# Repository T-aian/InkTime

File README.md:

# Documentație de Arhitectură și Inginerie Hardware: Sistemul Wearable InkTime

## 1. Introducere

Proiectul InkTime reprezintă o inițiativă tehnologică ambițioasă de a dezvolta un smartwatch open-source, optimizat pentru costuri reduse și manufacturabilitate la scară largă, fără a face compromisuri în ceea ce privește fiabilitatea sau performanța.

### 1.1. Structura Proiectului

- **Hardware/**: Găzduiește definițiile fundamentale ale circuitului. Aici se regăsesc fișierul schematic (.sch), alături de fișierul board-ului (.brd).
- **Manufacturing/**: Conține arhiva esențială pentru fabrica de PCB-uri (gerbers.zip), care include straturile de cupru, măștile de lipire (solder mask), stratul de inscripționare (silkscreen) și fișierele de găurire (Excellon drill files). De asemenea, acest director include fișierul Bill of Materials (.bom), detaliind componentele utilizate, și fișierul Pick and Place (.cpl), care mapează coordonatele carteziene (X, Y) și rotația fiecărei componente pentru echipamentele automate de asamblare.
- **Mechanical/**: Include modelul 3D integrat al dispozitivului în format .step și format nativ Fusion360. Acest model cuprinde PCB-ul populat cu componente, geometria exactă a bateriei Li-Po, ecranul LCD, motorul haptic (shaker) și șasiul carcasei într-o vizualizare detaliată de tip "exploded view".
- **Images/**: Un director vizual care conține randări fotorealiste ale PCBA-ului (Printed Circuit Board Assembly) și ilustrează modul de potrivire mecanică a plăcii în carcasă, servind drept ghid vizual pentru procedurile de asamblare manuală.

## 2. Arhitectura de Sistem și Diagrama Bloc

Filosofia de design a smartwatch-ului InkTime se bazează pe o topologie modulară, distribuită în jurul unui nod central de procesare (System-on-Chip). Diagrama bloc de mai jos ilustrează interconectarea magistralelor de date, a traseelor de putere și a modulelor periferice. Sistemul este împărțit în patru domenii funcționale majore: Domeniul de Putere (Power Tree), Domeniul de Procesare și Comunicație RF, Domeniul Senzorial și Domeniul Interfeței cu Utilizatorul (UI/HMI).

Fluxul de operare este dictat de nRF52840, care gestionează stările de energie (Power States) ale întregului sistem. Modulul comunică asincron prin magistrala I2C (Inter-Integrated Circuit) cu senzorii (BMA423 pentru detecția mișcării, MAX17048 pentru starea bateriei, DRV2605 pentru feedback haptic) și sincron prin magistrala SPI (Serial Peripheral Interface) cu ecranul LCD. Etajul de alimentare separă procesul de încărcare (gestionat autonom de BQ25121A) de procesul de reglare a tensiunii (gestionat de RT6150AWSC), asigurând o tensiune logică de 3.3V indiferent de nivelul de descărcare al bateriei.

## 3. Bill of Materials (BOM)
Realizarea unui dispozitiv de masă la un cost competitiv impune o selecție a componentelor ancorată puternic în realitățile lanțului de aprovizionare (Supply Chain). Toate componentele majore au fost selectate din biblioteca producătorului asiatic JLCPCB, favorizând componentele "Basic" sau "Extended" aflate constant în stoc, evitând astfel întârzierile de aprovizionare.

De asemenea, pachetele fizice (footprints) au fost alese pentru a permite un asamblaj automatizat de mare viteză pe mașinile Pick and Place, respectând totodată cerința impusă de a utiliza exclusiv pachete SMD (Surface Mount Device).

| Componentă        | Descriere funcțională                                                                                      | JLCPCB Part #    | Link JLCPCB | Datasheet                                                                                                                                                                                                  |
| ----------------- | ---------------------------------------------------------------------------------------------------------- | ---------------- | ----------- | ---------------------------------------------------------------------------------------------------------------------------------------------------------------------------------------------------------- |
| nRF52840-QIAA-R   | System-on-Chip (SoC) ARM Cortex-M4F 64MHz, transceiver Bluetooth 5.0, 1MB Flash, 256KB RAM, pachet AQFN-73 | C190794          | [Link JLCPCB](https://jlcpcb.com/partdetail/NordicSemicon-NRF52840_QIAAR/C190794) | [https://files.seeedstudio.com/wiki/XIAO-BLE/Nano_BLE_MCU-nRF52840_PS_v1.1.pdf](https://files.seeedstudio.com/wiki/XIAO-BLE/Nano_BLE_MCU-nRF52840_PS_v1.1.pdf)                                             |
| MAX17048G+T10     | Fuel Gauge pentru baterii Li-Ion (1 celulă), algoritm ModelGauge, interfață I2C, pachet TDFN-8             | C2682616         | [Link JLCPCB](https://jlcpcb.com/partdetail/C2682616) | [https://www.analog.com/media/en/technical-documentation/data-sheets/max17048-max17049.pdf](https://www.analog.com/media/en/technical-documentation/data-sheets/max17048-max17049.pdf)                     |
| BMA423            | Accelerometru MEMS triaxial, 12 biți, step counter hardware, pachet LGA-12                                 | C189517          | [Link JLCPCB](https://www.lcsc.com/product-detail/C189517.html) | [https://watchy.sqfmi.com/assets/files/BST-BMA423-DS000-1509600-950150f51058597a6234dd3eaafbb1f0.pdf](https://watchy.sqfmi.com/assets/files/BST-BMA423-DS000-1509600-950150f51058597a6234dd3eaafbb1f0.pdf) |
| DRV2605YZFR       | Driver haptic smart-loop pentru motoare ERM/LRA, librărie Immersion, pachet DSBGA-9                        | C81079           | [Link JLCPCB](https://www.lcsc.com/product-detail/C81079.html) | [https://www.ti.com/lit/ds/symlink/drv2605.pdf](https://www.ti.com/lit/ds/symlink/drv2605.pdf)                                                                                                             |
| BQ25121AYBGR      | PMIC + încărcător Li-Po ultra low power (max 300mA), Ship Mode, pachet DSBGA-25                            | C111776          | [Link JLCPCB](https://jlcpcb.com/parts) | [https://www.ti.com/lit/ds/symlink/bq25121a.pdf](https://www.ti.com/lit/ds/symlink/bq25121a.pdf)                                                                                                           |
| RT6150AWSC        | Convertor DC-DC buck-boost (1.8V–5.5V → 3.3V), curent max 800mA, consum idle 60µA                          | C147971          | [Link JLCPCB](https://www.lcsc.com/product-detail/C147971.html) | [https://www.richtek.com/assets/product_file/RT6150A=RT6150B/DS6150AB-04.pdf](https://www.richtek.com/assets/product_file/RT6150A=RT6150B/DS6150AB-04.pdf)                                                 |
| KH-TYPE-C-16P     | Conector USB Type-C mamă, 16 pini, SMD, profil redus, 3A                                                   | C709357          | [Link JLCPCB](https://jlcpcb.com/partdetail/KH-TYPE-C-16P/C709357) | N/A                                                                                                                                                                                                        |
| USBLC6-2SC6       | Protecție ESD (TVS diode array), capacitance 2.5pF pentru linii USB                                        | C7519 / C2827654 | [Link JLCPCB](https://jlcpcb.com/partdetail/STMicroelectronics-USBLC62SC6/C7519) | [https://www.st.com/resource/en/datasheet/usblc6-2.pdf](https://www.st.com/resource/en/datasheet/usblc6-2.pdf)                                                                                             |
| 2450AT18B100E     | Antenă ceramică RF 2.45 GHz, eficiență ~76%, pachet SMD 1206                                               | C2836414         | [Link JLCPCB](https://jlcpcb.com/partdetail/JohansonTechnology-2450AT18B100/C2836414) | [https://www.johansontechnology.com/docs/1187/2450AT18B100_X8XXogU.pdf](https://www.johansontechnology.com/docs/1187/2450AT18B100_X8XXogU.pdf)                                                             |

## 4. Descrierea Exhaustivă a Funcționalității Hardware
Sistemul hardware a fost proiectat având ca prioritate absolută optimizarea balanței dintre performanța de calcul, capacitatea de interacțiune umană fluidă și un consum energetic de tip "ultra-low power". Modul în care aceste subsisteme interacționează determină direct fezabilitatea comercială a smartwatch-ului InkTime.
### 4.1. Nucleul de Procesare și Comunicație RF (nRF52840)
La baza sistemului se află integratul nRF52840-QIAA-R, un System-on-Chip (SoC) hibrid care combină logica unui microcontroler cu un transceiver radio de mare performanță. Funcționând la o frecvență de bază de 64 MHz, nucleul ARM Cortex-M4 include o unitate de calcul în virgulă mobilă (FPU - Floating Point Unit), esențială pentru procesarea accelerată a datelor senzoriale tridimensionale (cum ar fi cele generate de BMA423) și randarea elementelor grafice pe afișaj. Dispune de 1 MB memorie Flash internă și 256 KB memorie SRAM. Spațiul generos de memorie Flash permite integrarea sistemelor de operare de tip RTOS (precum Zephyr, frecvent utilizat în comunitatea open-source smartwatch) și implementarea de actualizări Over-The-Air (OTA) sigure.

Componenta de radiofrecvență a SoC-ului este extrem de performantă, suportând tehnologia Bluetooth 5.0 Low Energy (BLE), alături de protocoale precum Thread, Zigbee și rețele proprietare de 2.4 GHz. Dispozitivul are o sensibilitate de recepție de -95 dBm la 1 Mbps și poate emite semnale la o putere configurabilă de la -20 dBm până la +8 dBm. Această versatilitate asigură că ceasul poate menține o legătură stabilă cu un terminal mobil (ex. smartphone) chiar și în medii electromagnetice congestionate, minimizând totodată consumul bateriei adaptând puterea de transmisie. Securitatea pachetelor de date BLE este garantată de coprocesorul intern ARM TrustZone CryptoCell 310, care realizează criptare hardware AES/ECB asincron, degrevând procesorul principal.

Antena ceramică tip SMD (2450AT18B100E) este montată la extremitatea plăcii și este un dispozitiv de tip LTCC (Low Temperature Co-fired Ceramic), proiectat de Johanson Technology. Oferind o eficiență de 76%, antena necesită un design restrictiv al planului de masă pentru a nu-și altera impedanța caracteristică de 50 Ohmi.

### 4.2. Topologia de Alimentare și Managementul Bateriei (Power Delivery Network)

Tensiunea unei baterii clasice Litiu-Polimer (Li-Po) fluctuează considerabil în timpul ciclului său de descărcare, de la o valoare maximă de ~4.2V (complet încărcată) până la o tensiune de cut-off de aproximativ 3.0V. Pentru ca ecranul IPS și procesorul să ruleze constant, au nevoie de o sursă stabilă de energie. Aici intervine arhitectura "Power Tree" a dispozitivului InkTime.

### Etajul de Încărcare și Protecție (BQ25121A și USBLC6-2SC6):

Energia pătrunde în sistem prin intermediul conectorului KH-TYPE-C-16P, o versiune orizontală SMD care susține curenți nominali ridicați și care a fost preferată pentru profilul său plat. Liniile de date și alimentare ale portului USB sunt expuse mediului extern, devenind vulnerabile la descărcări electrostatice (ESD). Circuitul USBLC6-2SC6, conectat imediat după port, clamp-ează aceste tensiuni tranzitorii violente (clamping voltage de 17V) redirecționându-le în masă. Cu o capacitanță parazită de numai 2.5pF, acest cip nu degradează integritatea semnalului.

Tensiunea de 5V preluată (VBUS) este apoi rutată către circuitul de management al bateriei BQ25121AYBGR. Acest IC ultra-integrat a fost selectat în detrimentul soluțiilor clasice (precum TP4056) datorită capabilităților avansate de gestionare I2C și a unui consum de repaus (quiescent current) neglijabil. BQ25121A poate încărca bateria cu un curent controlat (maxim 300 mA), implementând ciclul standard CC-CV (Constant Current / Constant Voltage), dar mai important, dispune de un "Ship Mode". Prin activarea acestui mod, ceasul poate fi complet deconectat electronic de la baterie în timpul transportului și stocării în depozite, scăzând consumul bateriei sub 50nA, eliminând astfel riscul ca produsul să ajungă la consumator cu bateria "moartă".

### Etajul de Reglare a Tensiunii (RT6150AWSC):

Întreaga placă electronică funcționează la tensiunea standard de 3.3V (VCC / 3V3). Pentru a prelua variația bateriei de la 3.0V la 4.2V și a furniza constant 3.3V fără a disipa restul de putere ca pierdere termică (așa cum ar face un regulator liniar LDO), a fost integrat convertorul DC-DC Buck-Boost RT6150AWSC. Frecvența sa de comutație de 1 MHz permite utilizarea unor componente pasive magnetice (inductoare) mult mai mici, vitale pentru un design de tip smartwatch. Convertorul dispune de un "Power Save Mode" (PSM), care, în perioadele de consum redus, își scade frecvența de operare și trage din baterie un curent pasiv de doar 60 µA, menținând eficiențe mari la curenți mici.

### Monitorizarea Autonomiei (MAX17048G+T10):
În mod tradițional, monitorizarea capacității unei baterii implică inserarea unui rezistor tip "shunt" (coulomb counter) pe traseul de retur, ceea ce introduce pierderi resistive constante. InkTime utilizează integratul MAX17048G+T10. Acest fuel-gauge citește exclusiv tensiunea celulei (VCELL) și folosește un model matematic proprietar (ModelGauge™) pentru a estima Starea de Încărcare (State-of-Charge / SOC) cu o toleranță a erorii extrem de redusă, raportând datele către nRF52840 pe magistrala I2C. Prin eliminarea rezistorului de măsurare și o stare internă "Hibernate" în care consumă doar 3 µA, se economisește spațiu vital pe PCB și energie prețioasă.

### 4.3. Modulul Senzorial (Accelerometrul BMA423)
Pentru monitorizarea cinematică a purtătorului s-a implementat accelerometrul MEMS digital BMA423, proiectat de Bosch Sensortec. Acest senzor din clasa senzorilor "inteligenți" a fost creat special pentru industria wearable. În locul eșantionării constante și transferării a mii de pachete de date brute (Raw Acceleration Data) pe magistrala I2C către MCU – proces ce ar drena rapid bateria – BMA423 dispune de logică procesuală internă.
Funcția sa nativă de pedometru (Step Counter) analizează algoritmic tiparele de accelerație și numără pașii independent, menținând un consum total de putere redus până la pragul de 13 µA – 25 µA. Informația este stocată într-un buffer intern (FIFO de 1 kByte) de unde poate fi interogată ocazional de MCU. Suplimentar, funcțiile hardware de recunoaștere a mișcării identifică acțiunile de ridicare a brațului spre ochi ("Tilt-on-Wrist") sau bătăi ("Tap/Double Tap") și emit un impuls asincron pe un pin de întrerupere dedicat (INT), ordonând procesorului nRF52840 să iasă din modul System OFF/ON Sleep.

### 4.5. Feedback Haptic Avansat (DRV2605YZFR)

Alerta tactilă a utilizatorului trebuie să fie precisă, evitându-se "zgomotul" tactil al motoarelor dezechilibrate tradiționale. Implementarea include integratul DRV2605YZFR de la Texas Instruments, un driver haptic de înaltă finețe în pachet miniatural DSBGA (chip-scale package). Acest circuit, comunicând prin I2C, integrează o arhitectură de control "Smart-Loop" ce scurtează masiv timpii de accelerare (Startup Time ~ 0.7ms) și frânare ai motorului.
Mecanismul intern monitorizează constant forța contra-electromotoare (BEMF) indusă de motor pe liniile de acționare. Printr-o secvență de calibrare automată, DRV2605 detectează frecvența de rezonanță mecanică a actuatoarelor de tip LRA (Linear Resonant Actuator) și le acționează precis pe acea frecvență, extrăgând forță vibratorie dublă și economisind până la 50% din energia pe care ar fi risipit-o un driver liniar clasic cu punte H. Integratul include o memorie pre-încărcată cu peste 100 de efecte tactile licențiate de compania Immersion, permițând dezvoltatorilor software să selecteze simplu (via I2C) profilul de vibrație dorit (e.g., un „click” scurt de confirmare, o vibrație lungă de alertă), în loc să folosească comutații PWM manuale de la microcontroler. Când nu rulează nicio secvență, consumul driver-ului decade la sub 2 µA.

## 5. Alocarea și Justificarea Mapării Pinilor la nRF52840

SoC-ul nRF52840 oferă o matrice flexibilă (crossbar) pentru alocarea funcțiilor periferice (I2C, SPI, UART, PWM) către majoritatea pinilor GPIO. Cu toate acestea, această libertate este guvernată de reguli fizice imuabile detaliate în Specificațiile de Produs Nordic. Anumiți pini (e.g. P0.02, P0.03, P0.30, P1.15 etc.) sunt clasați arhitectural ca "Standard drive, low frequency I/O only", fiind optimizați exclusiv pentru semnale care nu depășesc 10 kHz. Ignorarea acestei limitări și forțarea unor magistrale rapide (cum ar fi clock-ul SPI la 8 MHz) pe acești pini va conduce la distorsiuni de formă a undei, diafonie radio (interferențe cu semnalul BLE de 2.4GHz) și emisii electromagnetice care pot eșua un test de certificare FCC/CE.

## 6. Analiza Bugetului Energetic și Estimarea Autonomiei Bateriei
Pentru a garanta că proiectul InkTime reprezintă o alternativă fezabilă pe piață, trebuie obținut un echilibru delicat între volumul intern restrâns al dispozitivului – care dictează utilizarea unei baterii Li-Po miniaturale de aproximativ 200 mAh (tensiune nominală 3.7V, tensiune maximă 4.2V) – și consumul diverselor componente electronice.

Mai jos prezentăm un calcul teoretic detaliat al consumului, divizat în cele două stări absolute de utilizare: Starea de Repaus (Sleep Mode) și Starea Activă (Peak Load). Calculele sunt preluate din informațiile stricte oferite de foile de catalog oficiale (Datasheets).

### 6.1. Consumul în Modul de Repaus (System Sleep State)

Un smartwatch își petrece majoritatea timpului (~90–95%) în stare de repaus, cu ecranul oprit. În acest mod:

- sistemul rulează în System ON Sleep (specific nRF52840)
- RAM-ul rămâne alimentat
- RTC-ul este activ
- BLE funcționează în mod Advertising periodic

Consum:
| Componentă     | Consum tipic | Condiție / Justificare                                        |
| -------------- | ------------ | ------------------------------------------------------------- |
| nRF52840 SoC   | ~1.5 µA      | System ON, CPU în WFI (Wait For Interrupt), RTC activ         |
| Radio BLE      | ~3.8 µA      | Advertising periodic (interval ~10s)                          |
| BMA423         | ~13.0 µA     | Low-power mode, sampling redus (~50 Hz), step detection activ |
| MAX17048       | ~3.0 µA      | Hibernate mode, măsurători rare                               |
| DRV2605        | ~1.75 µA     | Standby complet (shutdown)                                    |
| BQ25121A       | ~0.7 µA      | Leakage cu USB deconectat                                     |
| RT6150AWSC     | ~60.0 µA     | Quiescent current (DC-DC activ în Power Save Mode)            |
| PCB (rezidual) | ~10.0 µA     | Leakage pasive + pull-up-uri I2C                              |

**Consum total:** 
`TOTAL SLEEP ≈ 93.75 µA (0.093 mA)`

### 6.2. Consumul în Mod Activ (Peak Load State)

În modul activ (utilizatorul interacționează cu ceasul):
- display-ul este aprins
- BLE transmite date
- motorul haptic poate fi activ

| Componentă           | Consum Peak  | Condiție / Justificare                     |
| -------------------- | ------------ | ------------------------------------------ |
| Display e-ink      | ~5 – 15 mA (peak) | Doar în timpul refresh-ului (~200–500 ms). Consum ≈ 0 între refresh-uri |
| nRF52840 (CPU + BLE) | ~4.8 – 15 mA | TX BLE + procesare SPI pentru display      |
| BMA423               | ~0.15 mA     | High-performance mode (gesturi complexe)   |
| DRV2605 + motor      | ~60 – 80 mA  | Vibrație activă (ERM/LRA startup)          |

**Consum total:** 
`TOTAL ACTIVE ≈ 10 – 90 mA`

### 6.3 Durată de viață Estimativă

Pe baza bugetelor de consum estimate, autonomia sistemului poate fi aproximată considerând un scenariu realist de utilizare: ~95% din timp în modul sleep (~0.093 mA) și ~5% în modul activ (~50 mA mediu). Curentul mediu rezultat este:

`I_med ≈ 0.95 × 0.093 mA + 0.05 × 50 mA ≈ 2.58 mA`

Pentru o baterie Li-Po de 200 mAh, rezultă o durată de funcționare de aproximativ:

`T ≈ 200 mAh / 5.1 mA ≈ 77 ore (~3-4 zile)`

În practică, ținând cont de pierderile din conversia de tensiune (eficiența ~90% a regulatorului) și variațiile de utilizare (ex.vibrații frecvente), autonomia reală va fi în intervalul 4-5 zile, ceea ce este tipic pentru un smartwatch cu e-ink și funcții BLE active.

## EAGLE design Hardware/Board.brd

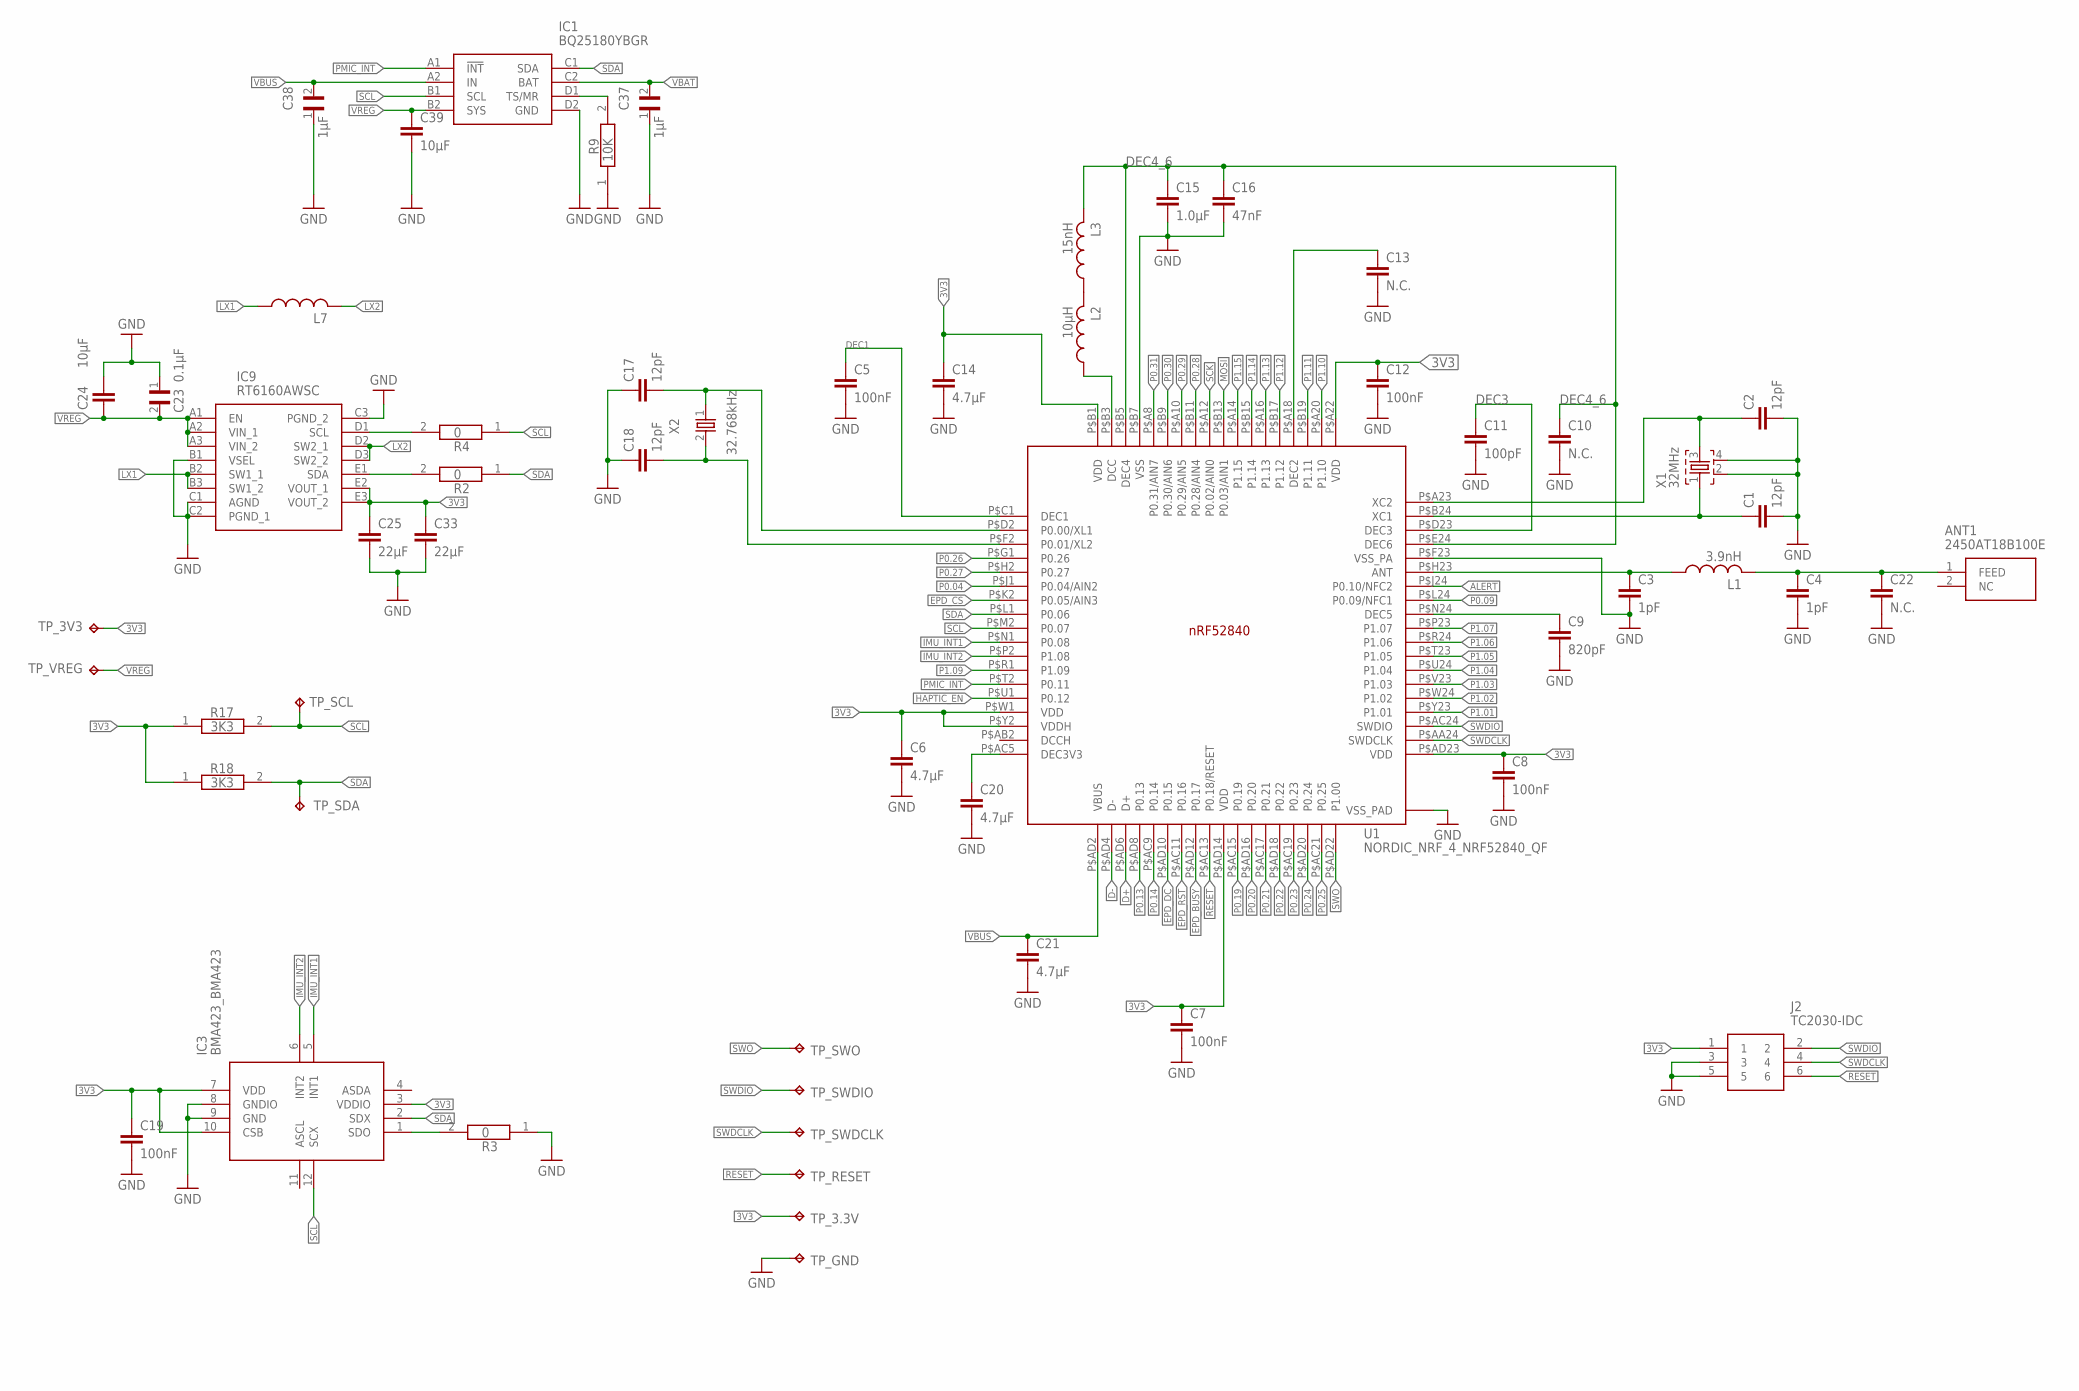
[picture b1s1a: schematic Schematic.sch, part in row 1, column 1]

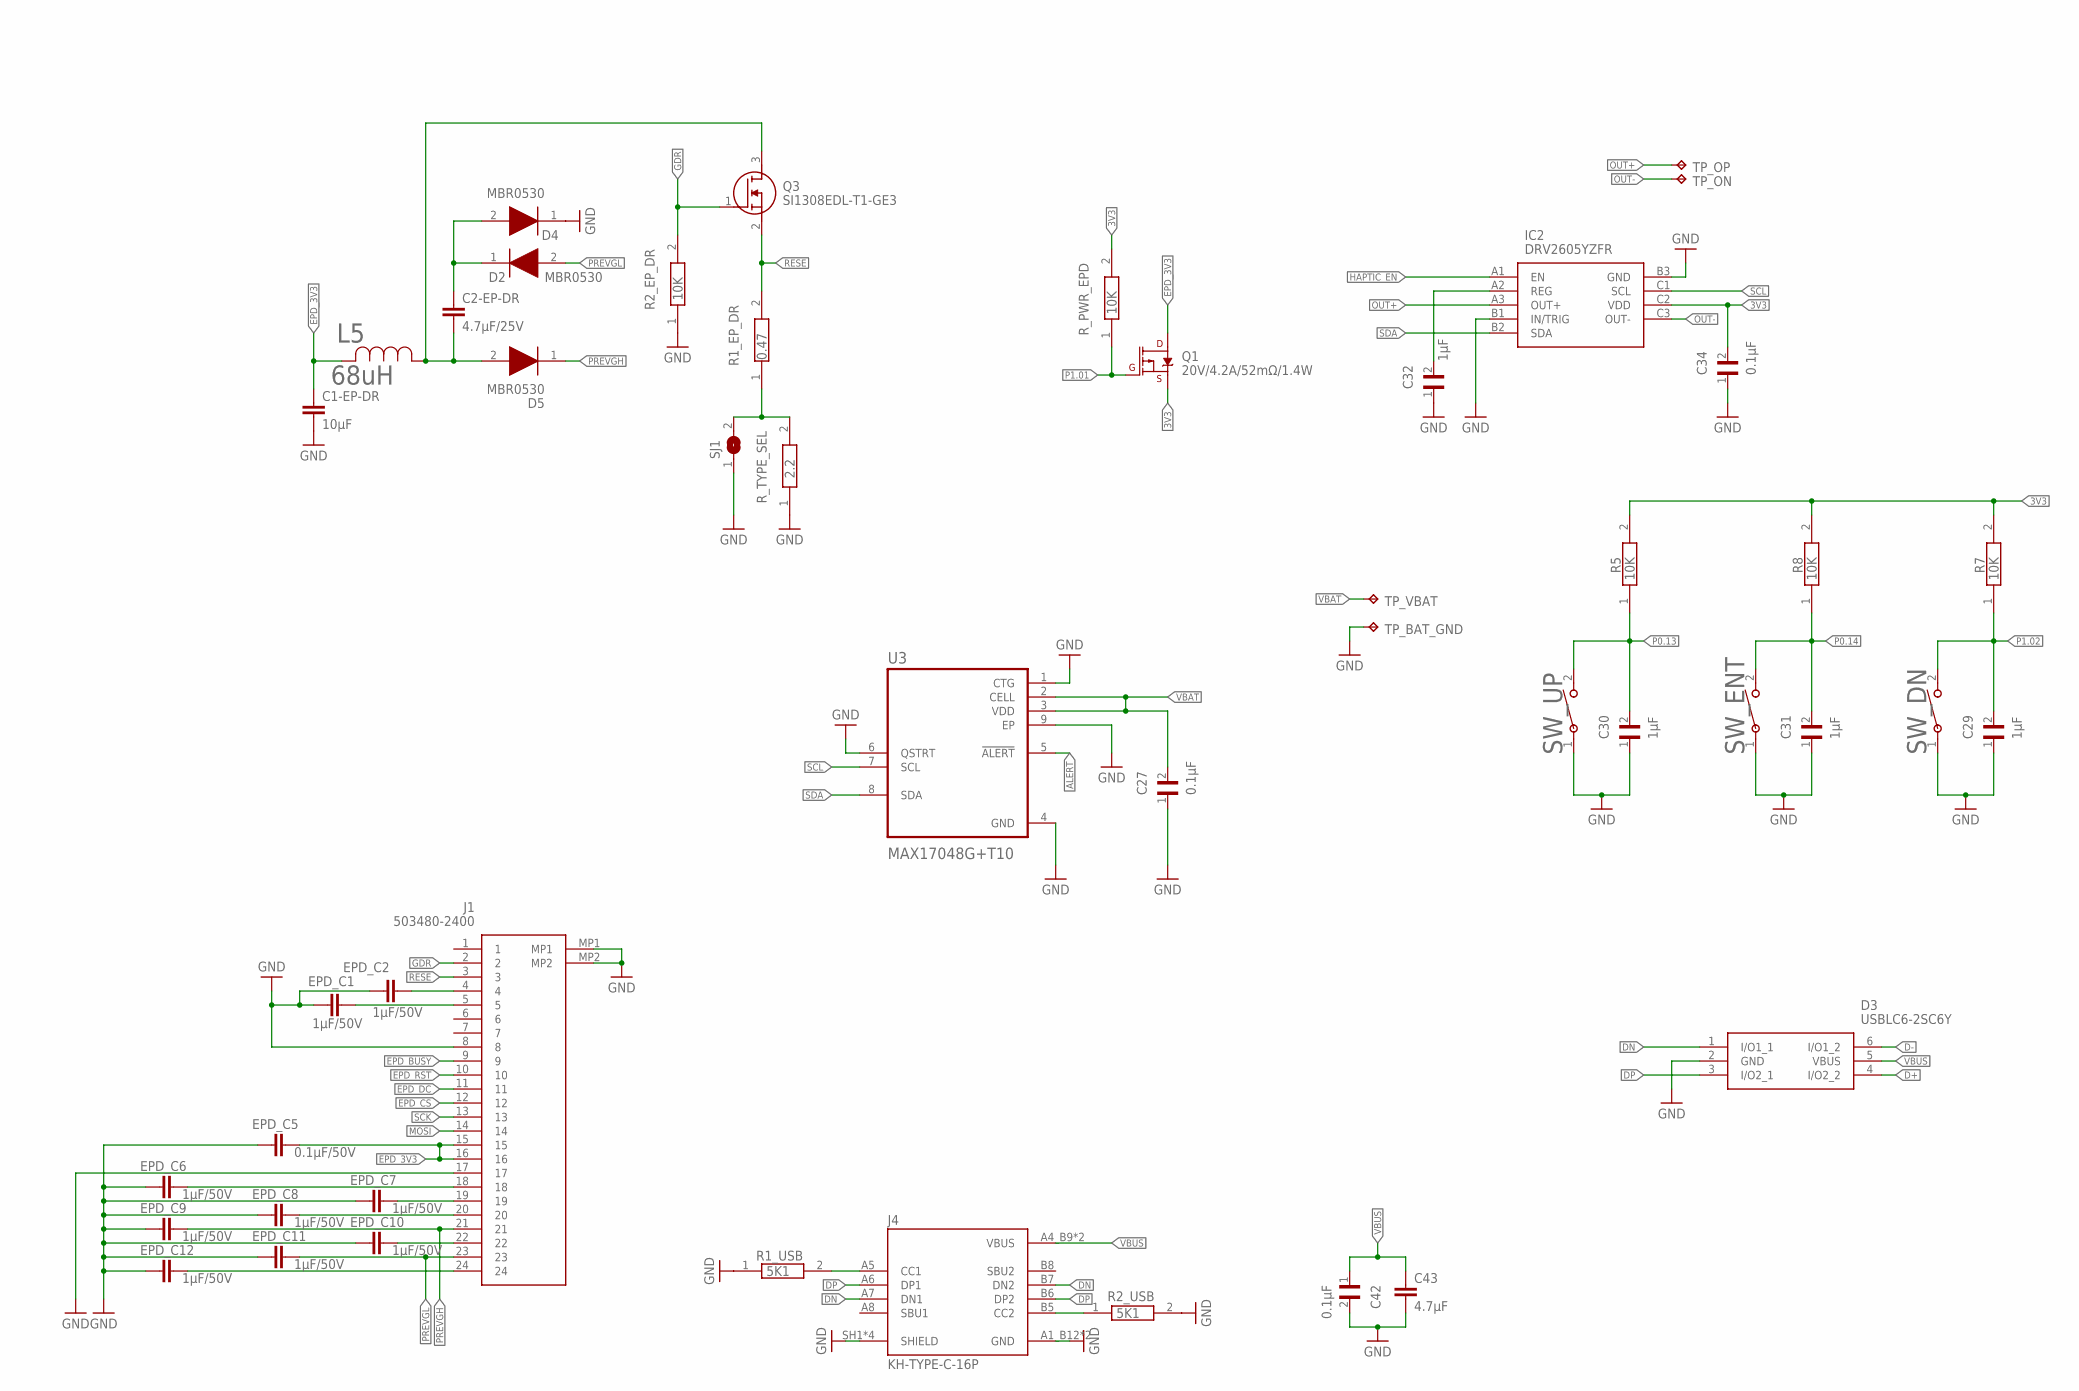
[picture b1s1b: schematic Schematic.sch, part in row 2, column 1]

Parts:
ANT1: 2450AT18B100E; 2450AT18B100E_ANTC3216X140N
C1, C2, C17, C18: 12pF; NORDIC_NRF_3_RESC0201_L
C1-EP-DR, C24, C39: 10μF; NORDIC_NRF_3_RESC0402_L
C2-EP-DR: 4.7μF/25V; NORDIC_NRF_3_RESC0402_L
C3, C4: 1pF; NORDIC_NRF_3_RESC0201_L
C5, C7, C8, C12, C19: 100nF; NORDIC_NRF_3_RESC0201_L
C6, C14, C20, C21: 4.7µF; NORDIC_NRF_3_RESC0402_L
C9: 820pF; NORDIC_NRF_3_RESC0201_L
C10, C13, C22: N.C.; NORDIC_NRF_3_RESC0201_L
C11: 100pF; NORDIC_NRF_3_RESC0201_L
C15: 1.0µF; NORDIC_NRF_3_RESC0402_L
C16: 47nF; NORDIC_NRF_3_RESC0201_L
C23, C27, C34, C42: 0.1μF; GRM011R60J152KE01L_2_CAPC0201X13N
C25, C33: 22μF; NORDIC_NRF_3_RESC0402_L
C29, C30, C31, C32, C37, C38: 1μF; GRM011R60J152KE01L_2_CAPC0201X13N
C43: 4.7μF; NORDIC_NRF_3_RESC0402_L
D2, D4, D5: MBR0530; ESP32_C6_LIBRARY_5_SOD3716X135N
D3: USBLC6-2SC6Y; ESP32_C6_LIBRARY_3_SOT95P280X145-6N
EPD_C1, EPD_C2, EPD_C6, EPD_C7, EPD_C8, EPD_C9, EPD_C10, EPD_C11, EPD_C12: 1μF/50V; NORDIC_NRF_3_RESC0402_L
EPD_C5: 0.1μF/50V; NORDIC_NRF_3_RESC0201_L
IC1: BQ25180YBGR; BQ25180YBGR_BGA8C40P2X4_100X155X50
IC2: DRV2605YZFR; DRV2605YZFR_BGA9C50P3X3_144X144X62
IC3: BMA423_BMA423
IC9: RT6160AWSC; RT6160AWSC_BGA15C40P3X5_140X230X60
J1: 503480-2400; 503480-2400_5034802400
J2: TC2030-IDC; TC2030-IDC_TC2030IDC
J4: KH-TYPE-C-16P; KH-TYPE-C-16P_KINGHELM_KH-TYPE-C-16P
L1: 3.9nH; NORDIC_NRF_2_RESC0402_L
L2: 10µH; NORDIC_NRF_2_RESC0402_L
L3: 15nH; NORDIC_NRF_2_RESC0402_L
L5: 68uH; ESP32_C6_LIBRARY_2_IND_4828-WE-TPC_WRE
L7: NORDIC_NRF_2_INDUCTOR_0402_L; NORDIC_NRF_2_RESC0402_L
Q1: 20V/4.2A/52mΩ/1.4W; ESP32_C6_LIBRARY_4_ESP32_C6_LIBRARY_4_ESP32_C6_LIBRARY_4_ES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
Q3: SI1308EDL-T1-GE3; ESP32_C6_LIBRARY_6_SOT65P210X110-3N
R1_EP_DR: 0.47; CPF0201D7K68C1_0201
R1_USB, R2_USB: 5K1; CPF0201D7K68C1_0201
R2, R3, R4: 0; CPF0201D7K68C1_0201
R2_EP_DR, R5, R7, R8, R9: 10K; CPF0201D7K68C1_0201
R17, R18: 3K3; CPF0201D7K68C1_0201
R_PWR_EPD: 10K; CPF0201D7K68C1_0201
R_TYPE_SEL: 2.2; CPF0201D7K68C1_0201
SJ1: ESP32_C6_LIBRARY_7_JUMPER_SJ
SW_DN: 2025-10-22_07-23-44_LIBRARY_EVP-AKE31ASW_EVP-AKE3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; 2025-10-22_07-23-44_LIBRARY_SW_EVP-AKE31A_PAN
SW_ENT: 2025-10-22_07-23-44_LIBRARY_EVP-AKE31ASW_EVP-AKE3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; 2025-10-22_07-23-44_LIBRARY_SW_EVP-AKE31A_PAN
SW_UP: 2025-10-22_07-23-44_LIBRARY_EVP-AKE31ASW_EVP-AKE3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; 2025-10-22_07-23-44_LIBRARY_SW_EVP-AKE31A_PAN
TP_3.3V, TP_3V3: HECTOR_WATCH_1_TPTP20R; HECTOR_WATCH_1_TP20R
TP_BAT_GND: HECTOR_WATCH_1_TPTP20R; HECTOR_WATCH_1_TP20R
TP_GND: HECTOR_WATCH_1_TPTP20R; HECTOR_WATCH_1_TP20R
TP_ON: HECTOR_WATCH_1_TPTP20R; HECTOR_WATCH_1_TP20R
TP_OP: HECTOR_WATCH_1_TPTP20R; HECTOR_WATCH_1_TP20R
TP_RESET: HECTOR_WATCH_1_TPTP20R; HECTOR_WATCH_1_TP20R
TP_SCL: HECTOR_WATCH_1_TPTP20R; HECTOR_WATCH_1_TP20R
TP_SDA: HECTOR_WATCH_1_TPTP20R; HECTOR_WATCH_1_TP20R
TP_SWDCLK: HECTOR_WATCH_1_TPTP20R; HECTOR_WATCH_1_TP20R
TP_SWDIO: HECTOR_WATCH_1_TPTP20R; HECTOR_WATCH_1_TP20R
TP_SWO: HECTOR_WATCH_1_TPTP20R; HECTOR_WATCH_1_TP20R
TP_VBAT: HECTOR_WATCH_1_TPTP20R; HECTOR_WATCH_1_TP20R
TP_VREG: HECTOR_WATCH_1_TPTP20R; HECTOR_WATCH_1_TP20R
U1: NORDIC_NRF_4_NRF52840_QF; NORDIC_NRF_4_AQFN50P700X700X85_HS-74N
U3: MAX17048G+T10; ESP32_C6_LIBRARY_SON50P200X200X80-9N
X1: 32MHz; NORDIC_NRF_BT-XTAL_2016_N
X2: 32.768kHz; NORDIC_NRF_1_XTAL_3215_N

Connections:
3V3: C6.1, C7.1, C8.1, C12.1, C14.1, C19.1, C25.1, C33.1, C34.2, IC2.C2 (VDD), IC3.3 (VDDIO), IC3.7 (VDD), IC3.10 (CSB), IC9.E2 (VOUT_1), IC9.E3 (VOUT_2), J2.1, Q1.2 (S), R5.2, R7.2, R8.2, R17.1, R18.1, R_PWR_EPD.2, TP_3.3V.TP, TP_3V3.TP, U1.P$A22 (VDD), U1.P$AD14 (VDD), U1.P$AD23 (VDD), U1.P$B1 (VDD), U1.P$W1 (VDD), U1.P$Y2 (VDDH)
ALERT: U1.P$J24 (P0.10/NFC2), U3.5 (!ALERT)
D+: D3.4 (I/O2_2), U1.P$AD6 (D+)
D-: D3.6 (I/O1_2), U1.P$AD4 (D-)
DEC1: C5.1, U1.P$C1 (DEC1)
DEC3: C11.1, U1.P$D23 (DEC3)
DEC4_6: C10.1, C15.1, C16.1, L3.2, U1.P$B5 (DEC4), U1.P$E24 (DEC6)
DN: D3.1 (I/O1_1), J4.A7 (DN1), J4.B7 (DN2)
DP: D3.3 (I/O2_1), J4.A6 (DP1), J4.B6 (DP2)
EPD_3V3: C1-EP-DR.1, EPD_C5.2, J1.15, J1.16, L5.2, Q1.3 (D)
EPD_BUSY: J1.9, U1.P$AD12 (P0.17)
EPD_CS: J1.12, U1.P$K2 (P0.05/AIN3)
EPD_DC: J1.11, U1.P$AD10 (P0.15)
EPD_RST: J1.10, U1.P$AC11 (P0.16)
GDR: J1.2, Q3.1 (G), R2_EP_DR.2
GND: C1.2, C1-EP-DR.2, C2.2, C3.2, C4.2, C5.2, C6.2, C7.2, C8.2, C9.2, C10.2, C11.2, C12.2, C13.2, C14.2, C15.2, C16.2, C17.1, C18.1, C19.2, C20.2, C21.2, C22.2, C23.1, C24.1, C25.2, C27.1, C29.1, C30.1, C31.1, C32.1, C33.2, C34.1, C37.1, C38.1, C39.2, C42.2, C43.2, D3.2 (GND), D4.1 (K), EPD_C1.1, EPD_C2.1, EPD_C5.1, EPD_C6.2, EPD_C7.2, EPD_C8.2, EPD_C9.2, EPD_C10.2, EPD_C11.2, EPD_C12.2, IC1.D2 (GND), IC2.B1 (IN/TRIG), IC2.B3 (GND), IC3.8 (GNDIO), IC3.9 (GND), IC9.B1 (VSEL), IC9.C1 (AGND), IC9.C2 (PGND_1), IC9.C3 (PGND_2), J1.8, J1.17, J1.MP1, J1.MP2, J2.3, J2.5, J4.A1_B12 (GND), J4.A12_B1 (GND), J4.SH1 (SHIELD), J4.SH2 (SHIELD), J4.SH3 (SHIELD), J4.SH4 (SHIELD), R1_USB.1, R2_EP_DR.1, R2_USB.2, R3.1, R9.1, R_TYPE_SEL.1, SJ1.1, SW_DN.1, SW_ENT.1, SW_UP.1, TP_BAT_GND.TP, TP_GND.TP, U1.P$74 (VSS_PAD), U1.P$75 (VSS_PAD), U1.P$76 (VSS_PAD), U1.P$77 (VSS_PAD), U1.P$78 (VSS_PAD), U1.P$79 (VSS_PAD), U1.P$80 (VSS_PAD), U1.P$81 (VSS_PAD), U1.P$82 (VSS_PAD), U1.P$83 (VSS_PAD), U1.P$84 (VSS_PAD), U1.P$85 (VSS_PAD), U1.P$86 (VSS_PAD), U1.P$87 (VSS_PAD), U1.P$88 (VSS_PAD), U1.P$89 (VSS_PAD), U1.P$90 (VSS_PAD), U1.P$B7 (VSS), U1.P$F23 (VSS_PA), U3.1 (CTG), U3.4 (GND), U3.6 (QSTRT), U3.9 (EP), X1.2, X1.4
HAPTIC_EN: IC2.A1 (EN), U1.P$U1 (P0.12)
IMU_INT1: IC3.5 (INT1), U1.P$N1 (P0.08)
IMU_INT2: IC3.6 (INT2), U1.P$P2 (P1.08)
LX1: IC9.B2 (SW1_1), IC9.B3 (SW1_2), L7.1
LX2: IC9.D2 (SW2_1), IC9.D3 (SW2_2), L7.2
MOSI: J1.14, U1.P$B13 (P0.03/AIN1)
unnamed: C9.1, U1.P$N24 (DEC5)
unnamed: ANT1.1 (FEED), C4.1, C22.1, L1.2
unnamed: C3.1, L1.1, U1.P$H23 (ANT)
unnamed: C13.1, U1.P$A18 (DEC2)
unnamed: C2.1, U1.P$A23 (XC2), X1.3
unnamed: C1.1, U1.P$B24 (XC1), X1.1
unnamed: L2.2, L3.1
unnamed: L2.1, U1.P$B3 (DCC)
unnamed: C18.2, U1.P$F2 (P0.01/XL2), X2.2
unnamed: C17.2, U1.P$D2 (P0.00/XL1), X2.1
unnamed: IC3.1 (SDO), R3.2
unnamed: C20.1, U1.P$AC5 (DEC3V3)
unnamed: IC1.D1 (TS/MR), R9.2
unnamed: IC9.D1 (SCL), R4.2
unnamed: IC9.E1 (SDA), R2.2
unnamed: R1_EP_DR.1, R_TYPE_SEL.2, SJ1.2
unnamed: C2-EP-DR.1, D2.1 (K), D4.2 (A)
unnamed: EPD_C2.2, J1.4
unnamed: C2-EP-DR.2, D5.2 (A), L5.1, Q3.3 (D)
unnamed: EPD_C1.2, J1.5
unnamed: EPD_C6.1, J1.18
unnamed: C32.2, IC2.A2 (REG)
unnamed: EPD_C7.1, J1.19
unnamed: EPD_C8.1, J1.20
unnamed: EPD_C10.1, J1.22
unnamed: EPD_C12.1, J1.24
unnamed: J4.B5 (CC2), R2_USB.1
unnamed: J4.A5 (CC1), R1_USB.2
OUT+: IC2.A3 (OUT+), TP_OP.TP
OUT-: IC2.C3 (OUT-), TP_ON.TP
P0.04: U1.P$J1 (P0.04/AIN2)
P0.09: U1.P$L24 (P0.09/NFC1)
P0.13: C30.2, R5.1, SW_UP.2, U1.P$AD8 (P0.13)
P0.14: C31.2, R8.1, SW_ENT.2, U1.P$AC9 (P0.14)
P0.19: U1.P$AC15 (P0.19)
P0.20: U1.P$AD16 (P0.20)
P0.21: U1.P$AC17 (P0.21)
P0.22: U1.P$AD18 (P0.22)
P0.23: U1.P$AC19 (P0.23)
P0.24: U1.P$AD20 (P0.24)
P0.25: U1.P$AC21 (P0.25)
P0.26: U1.P$G1 (P0.26)
P0.27: U1.P$H2 (P0.27)
P0.28: U1.P$B11 (P0.28/AIN4)
P0.29: U1.P$A10 (P0.29/AIN5)
P0.30: U1.P$B9 (P0.30/AIN6)
P0.31: U1.P$A8 (P0.31/AIN7)
P1.01: Q1.1 (G), R_PWR_EPD.1, U1.P$Y23 (P1.01)
P1.02: C29.2, R7.1, SW_DN.2, U1.P$W24 (P1.02)
P1.03: U1.P$V23 (P1.03)
P1.04: U1.P$U24 (P1.04)
P1.05: U1.P$T23 (P1.05)
P1.06: U1.P$R24 (P1.06)
P1.07: U1.P$P23 (P1.07)
P1.09: U1.P$R1 (P1.09)
P1.10: U1.P$A20 (P1.10)
P1.11: U1.P$B19 (P1.11)
P1.12: U1.P$B17 (P1.12)
P1.13: U1.P$A16 (P1.13)
P1.14: U1.P$B15 (P1.14)
P1.15: U1.P$A14 (P1.15)
PMIC_INT: IC1.A1 (!INT), U1.P$T2 (P0.11)
PREVGH: D5.1 (K), EPD_C9.1, J1.21
PREVGL: D2.2 (A), EPD_C11.1, J1.23
RESE: J1.3, Q3.2 (S), R1_EP_DR.2
RESET: J2.6, TP_RESET.TP, U1.P$AC13 (P0.18/RESET)
SCK: J1.13, U1.P$A12 (P0.02/AIN0)
SCL: IC1.B1 (SCL), IC2.C1 (SCL), IC3.12 (SCX), R4.1, R17.2, TP_SCL.TP, U1.P$M2 (P0.07), U3.7 (SCL)
SDA: IC1.C1 (SDA), IC2.B2 (SDA), IC3.2 (SDX), R2.1, R18.2, TP_SDA.TP, U1.P$L1 (P0.06), U3.8 (SDA)
SWDCLK: J2.4, TP_SWDCLK.TP, U1.P$AA24 (SWDCLK)
SWDIO: J2.2, TP_SWDIO.TP, U1.P$AC24 (SWDIO)
SWO: TP_SWO.TP, U1.P$AD22 (P1.00)
VBAT: C27.2, C37.2, IC1.C2 (BAT), TP_VBAT.TP, U3.2 (CELL), U3.3 (VDD)
VBUS: C21.1, C38.2, C42.1, C43.1, D3.5 (VBUS), IC1.A2 (IN), J4.A4_B9 (VBUS), J4.A9_B4 (VBUS), U1.P$AD2 (VBUS)
VREG: C23.2, C24.2, C39.1, IC1.B2 (SYS), IC9.A1 (EN), IC9.A2 (VIN_1), IC9.A3 (VIN_2), TP_VREG.TP

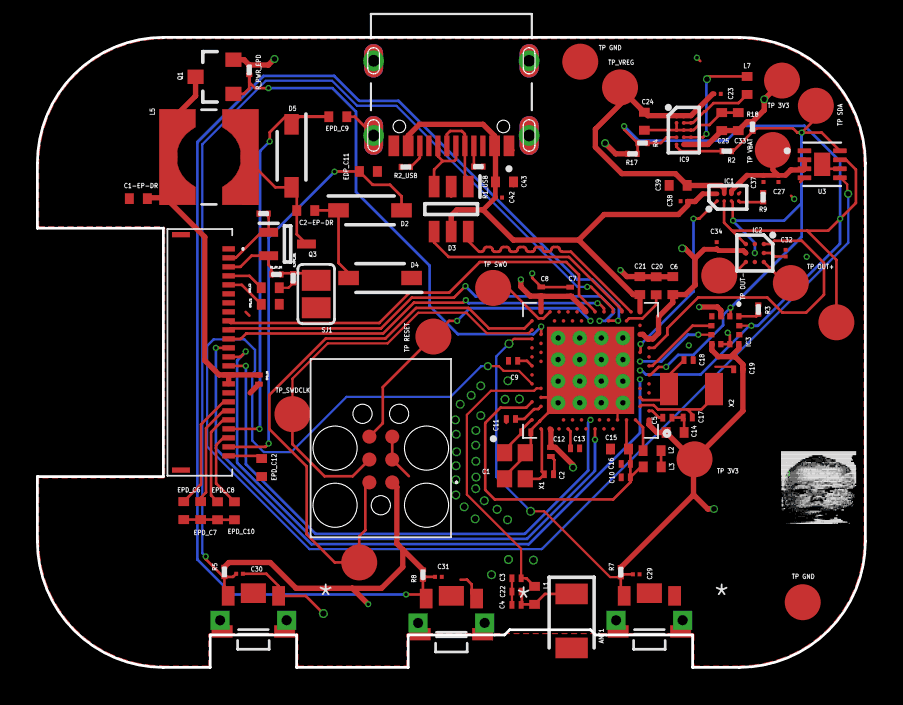
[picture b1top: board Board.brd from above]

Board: 4 copper layers, 46.0 x 35.0 mm, 105 parts (0 on the bottom side), 70 nets.

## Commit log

2026-04-10 Hardware
2026-04-16 Manufacturing
2026-04-16 Add License
    Added Apache License 2.0 to the project.
2026-04-17 Final stuff
2026-04-21 Antenna Cutout & Frames
2026-04-22 README
2026-04-22 README fix

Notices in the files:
parts and their libraries:
COPYRIGHT: Copyright (C) 2024 Ultra Librarian. All rights reserved.
COPYRIGHT: Copyright (C) 2025 Ultra Librarian. All rights reserved.
